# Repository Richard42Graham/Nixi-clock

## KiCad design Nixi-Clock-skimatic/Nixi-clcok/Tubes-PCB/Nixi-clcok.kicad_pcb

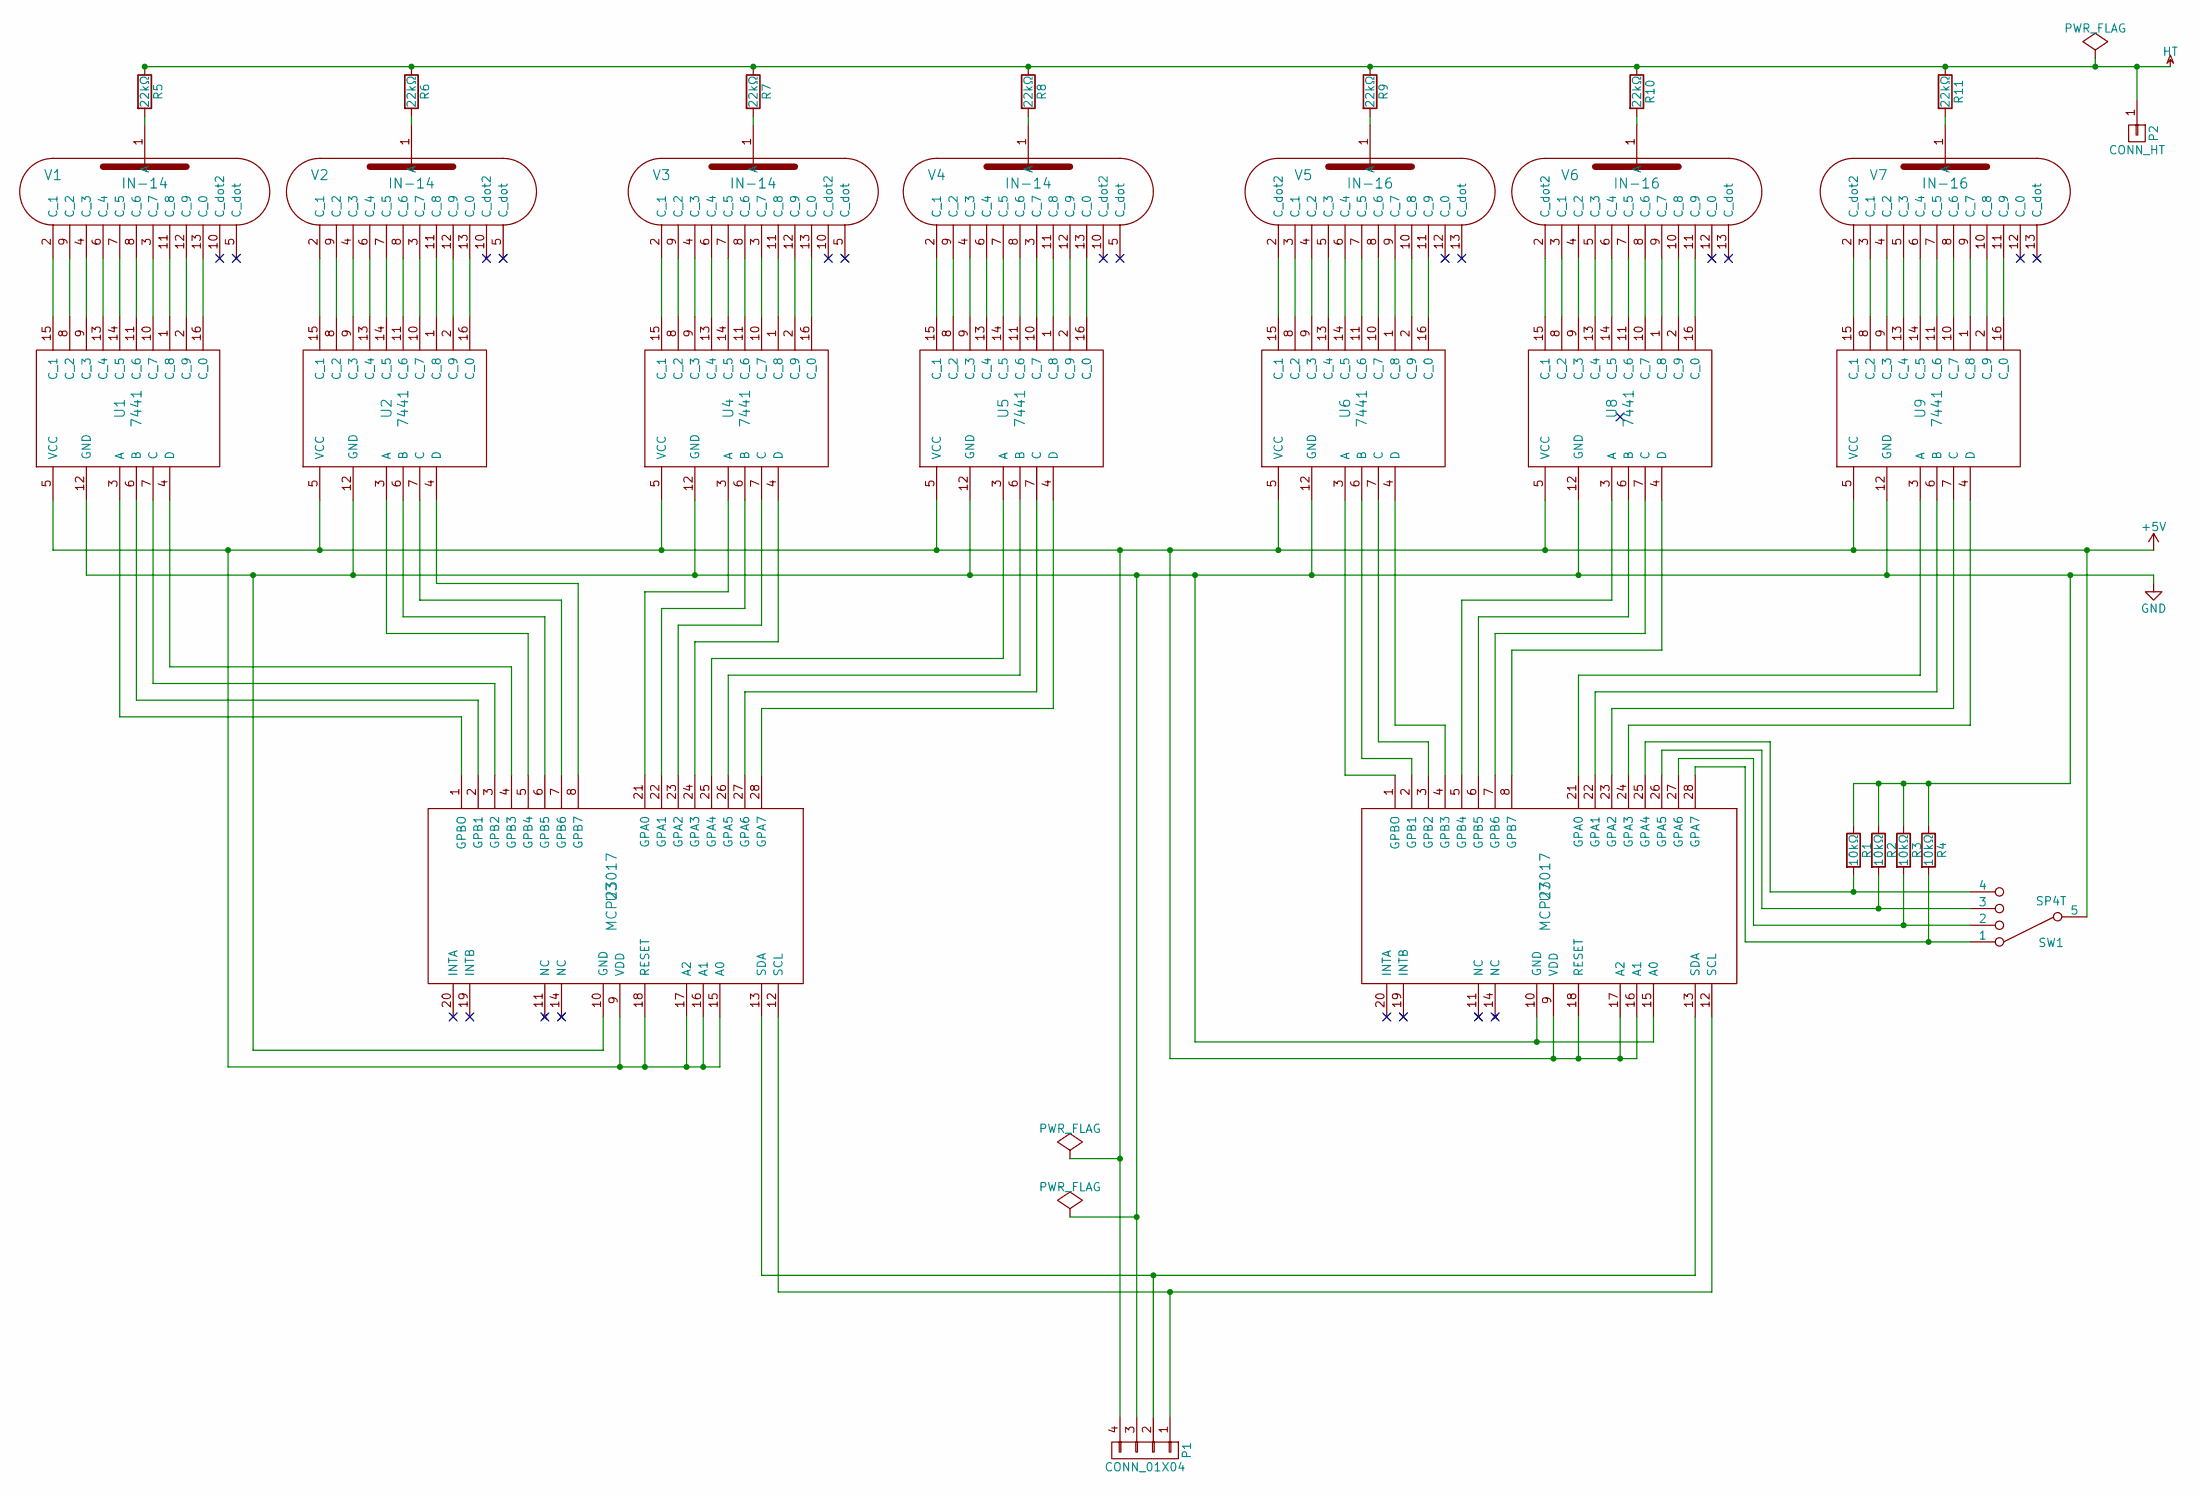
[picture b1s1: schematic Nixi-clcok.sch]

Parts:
P1: CONN_01X04; Pin_Header_Straight_1x04
P2: CONN_HT; Pin_Header_Straight_1x01
R1, R2, R3, R4: 10kΩ; R3
R5, R6, R7, R8, R9, R10, R11: 22kΩ; R3
SW1: SP4T; Pin_Header_Straight_1x05
U1, U2, U4, U5, U6, U8, U9: 7441; DIP-16_W7.62mm_LongPads
U3, U7: MCP23017; DIP-28_W7.62mm_LongPads
V1, V2, V3, V4: IN-14
V5, V6, V7: IN-16

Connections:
+5V: P1.4, SW1.5, U1.5 (VCC), U2.5 (VCC), U3.9 (VDD), U3.15 (A0), U3.16 (A1), U3.17 (A2), U3.18 (RESET), U4.5 (VCC), U5.5 (VCC), U6.5 (VCC), U7.9 (VDD), U7.16 (A1), U7.17 (A2), U7.18 (RESET), U8.5 (VCC), U9.5 (VCC)
GND: P1.3, R1.1, R2.1, R3.1, R4.1, U1.12 (GND), U2.12 (GND), U3.10 (GND), U4.12 (GND), U5.12 (GND), U6.12 (GND), U7.10 (GND), U7.15 (A0), U8.12 (GND), U9.12 (GND)
HT: P2.1, R5.1, R6.1, R7.1, R8.1, R9.1, R10.1, R11.1
unnamed: P1.1, U3.12 (SCL), U7.12 (SCL)
unnamed: P1.2, U3.13 (SDA), U7.13 (SDA)
unnamed: R1.2, SW1.4, U7.25 (GPA4)
unnamed: R2.2, SW1.3, U7.26 (GPA5)
unnamed: R3.2, SW1.2, U7.27 (GPA6)
unnamed: R4.2, SW1.1, U7.28 (GPA7)
unnamed: R5.2, V1.1 (A)
unnamed: R6.2, V2.1 (A)
unnamed: R7.2, V3.1 (A)
unnamed: R8.2, V4.1 (A)
unnamed: R9.2, V5.1 (A)
unnamed: R10.2, V6.1 (A)
unnamed: R11.2, V7.1 (A)
unnamed: U1.1 (C_8), V1.11 (C_8)
unnamed: U1.2 (C_9), V1.12 (C_9)
unnamed: U1.3 (A), U3.1 (GPBO)
unnamed: U1.4 (D), U3.4 (GPB3)
unnamed: U1.6 (B), U3.2 (GPB1)
unnamed: U1.7 (C), U3.3 (GPB2)
unnamed: U1.8 (C_2), V1.9 (C_2)
unnamed: U1.9 (C_3), V1.4 (C_3)
unnamed: U1.10 (C_7), V1.3 (C_7)
unnamed: U1.11 (C_6), V1.8 (C_6)
unnamed: U1.13 (C_4), V1.6 (C_4)
unnamed: U1.14 (C_5), V1.7 (C_5)
unnamed: U1.15 (C_1), V1.2 (C_1)
unnamed: U1.16 (C_0), V1.13 (C_0)
unnamed: U2.1 (C_8), V2.11 (C_8)
unnamed: U2.2 (C_9), V2.12 (C_9)
unnamed: U2.3 (A), U3.5 (GPB4)
unnamed: U2.4 (D), U3.8 (GPB7)
unnamed: U2.6 (B), U3.6 (GPB5)
unnamed: U2.7 (C), U3.7 (GPB6)
unnamed: U2.8 (C_2), V2.9 (C_2)
unnamed: U2.9 (C_3), V2.4 (C_3)
unnamed: U2.10 (C_7), V2.3 (C_7)
unnamed: U2.11 (C_6), V2.8 (C_6)
unnamed: U2.13 (C_4), V2.6 (C_4)
unnamed: U2.14 (C_5), V2.7 (C_5)
unnamed: U2.15 (C_1), V2.2 (C_1)
unnamed: U2.16 (C_0), V2.13 (C_0)
unnamed: U3.21 (GPA0), U4.3 (A)
unnamed: U3.22 (GPA1), U4.6 (B)
unnamed: U3.23 (GPA2), U4.7 (C)
unnamed: U3.24 (GPA3), U4.4 (D)
unnamed: U3.25 (GPA4), U5.3 (A)
unnamed: U3.26 (GPA5), U5.6 (B)
unnamed: U3.27 (GPA6), U5.7 (C)
unnamed: U3.28 (GPA7), U5.4 (D)
unnamed: U4.1 (C_8), V3.11 (C_8)
unnamed: U4.2 (C_9), V3.12 (C_9)
unnamed: U4.8 (C_2), V3.9 (C_2)
unnamed: U4.9 (C_3), V3.4 (C_3)
unnamed: U4.10 (C_7), V3.3 (C_7)
unnamed: U4.11 (C_6), V3.8 (C_6)
unnamed: U4.13 (C_4), V3.6 (C_4)
unnamed: U4.14 (C_5), V3.7 (C_5)
unnamed: U4.15 (C_1), V3.2 (C_1)
unnamed: U4.16 (C_0), V3.13 (C_0)
unnamed: U5.1 (C_8), V4.11 (C_8)
unnamed: U5.2 (C_9), V4.12 (C_9)
unnamed: U5.8 (C_2), V4.9 (C_2)
unnamed: U5.9 (C_3), V4.4 (C_3)
unnamed: U5.10 (C_7), V4.3 (C_7)
unnamed: U5.11 (C_6), V4.8 (C_6)
unnamed: U5.13 (C_4), V4.6 (C_4)
unnamed: U5.14 (C_5), V4.7 (C_5)
unnamed: U5.15 (C_1), V4.2 (C_1)
unnamed: U5.16 (C_0), V4.13 (C_0)
unnamed: U6.1 (C_8), V5.9 (C_7)
unnamed: U6.2 (C_9), V5.10 (C_8)
unnamed: U6.3 (A), U7.1 (GPBO)
unnamed: U6.4 (D), U7.4 (GPB3)
unnamed: U6.6 (B), U7.2 (GPB1)
unnamed: U6.7 (C), U7.3 (GPB2)
unnamed: U6.8 (C_2), V5.3 (C_1)
unnamed: U6.9 (C_3), V5.4 (C_2)
unnamed: U6.10 (C_7), V5.8 (C_6)
unnamed: U6.11 (C_6), V5.7 (C_5)
unnamed: U6.13 (C_4), V5.5 (C_3)
unnamed: U6.14 (C_5), V5.6 (C_4)
unnamed: U6.15 (C_1), V5.2 (C_dot2)
unnamed: U6.16 (C_0), V5.11 (C_9)
unnamed: U7.5 (GPB4), U8.3 (A)
unnamed: U7.6 (GPB5), U8.6 (B)
unnamed: U7.7 (GPB6), U8.7 (C)
unnamed: U7.8 (GPB7), U8.4 (D)
unnamed: U7.21 (GPA0), U9.3 (A)
unnamed: U7.22 (GPA1), U9.6 (B)
unnamed: U7.23 (GPA2), U9.7 (C)
unnamed: U7.24 (GPA3), U9.4 (D)
unnamed: U8.1 (C_8), V6.9 (C_7)
unnamed: U8.2 (C_9), V6.10 (C_8)
unnamed: U8.8 (C_2), V6.3 (C_1)
unnamed: U8.9 (C_3), V6.4 (C_2)
unnamed: U8.10 (C_7), V6.8 (C_6)
unnamed: U8.11 (C_6), V6.7 (C_5)
unnamed: U8.13 (C_4), V6.5 (C_3)
unnamed: U8.14 (C_5), V6.6 (C_4)
unnamed: U8.15 (C_1), V6.2 (C_dot2)
unnamed: U8.16 (C_0), V6.11 (C_9)
unnamed: U9.1 (C_8), V7.9 (C_7)
unnamed: U9.2 (C_9), V7.10 (C_8)
unnamed: U9.8 (C_2), V7.3 (C_1)
unnamed: U9.9 (C_3), V7.4 (C_2)
unnamed: U9.10 (C_7), V7.8 (C_6)
unnamed: U9.11 (C_6), V7.7 (C_5)
unnamed: U9.13 (C_4), V7.5 (C_3)
unnamed: U9.14 (C_5), V7.6 (C_4)
unnamed: U9.15 (C_1), V7.2 (C_dot2)
unnamed: U9.16 (C_0), V7.11 (C_9)

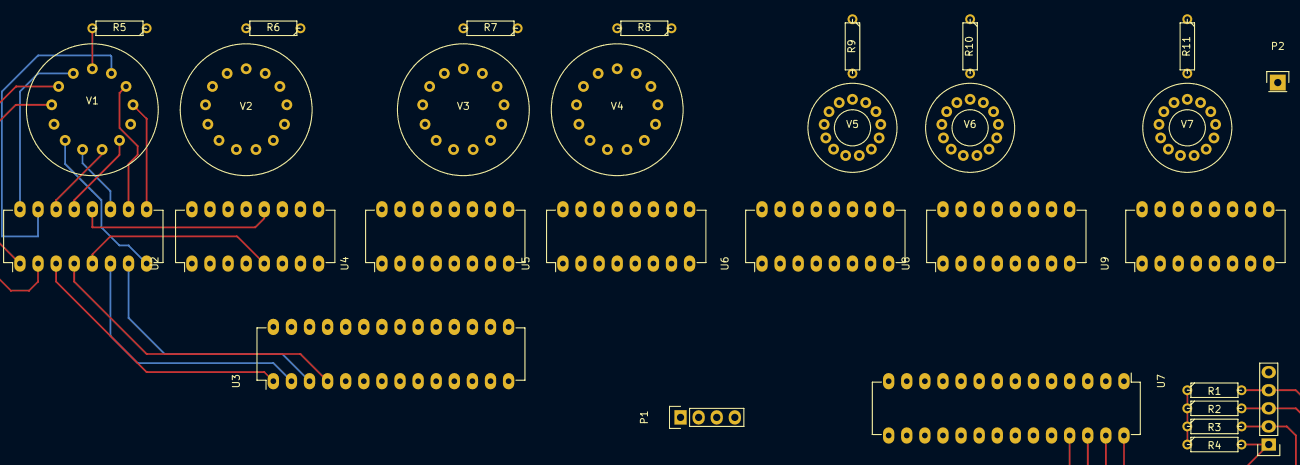
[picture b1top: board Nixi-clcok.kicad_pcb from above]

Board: 2 copper layers, 30 parts (0 on the bottom side), 114 nets.

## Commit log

2015-10-13 added data sheets
2015-10-16 added data sheets for more parts
2015-10-16 added some idear of the code structure
2015-10-31 added kicad circuit diograms and board for clock
